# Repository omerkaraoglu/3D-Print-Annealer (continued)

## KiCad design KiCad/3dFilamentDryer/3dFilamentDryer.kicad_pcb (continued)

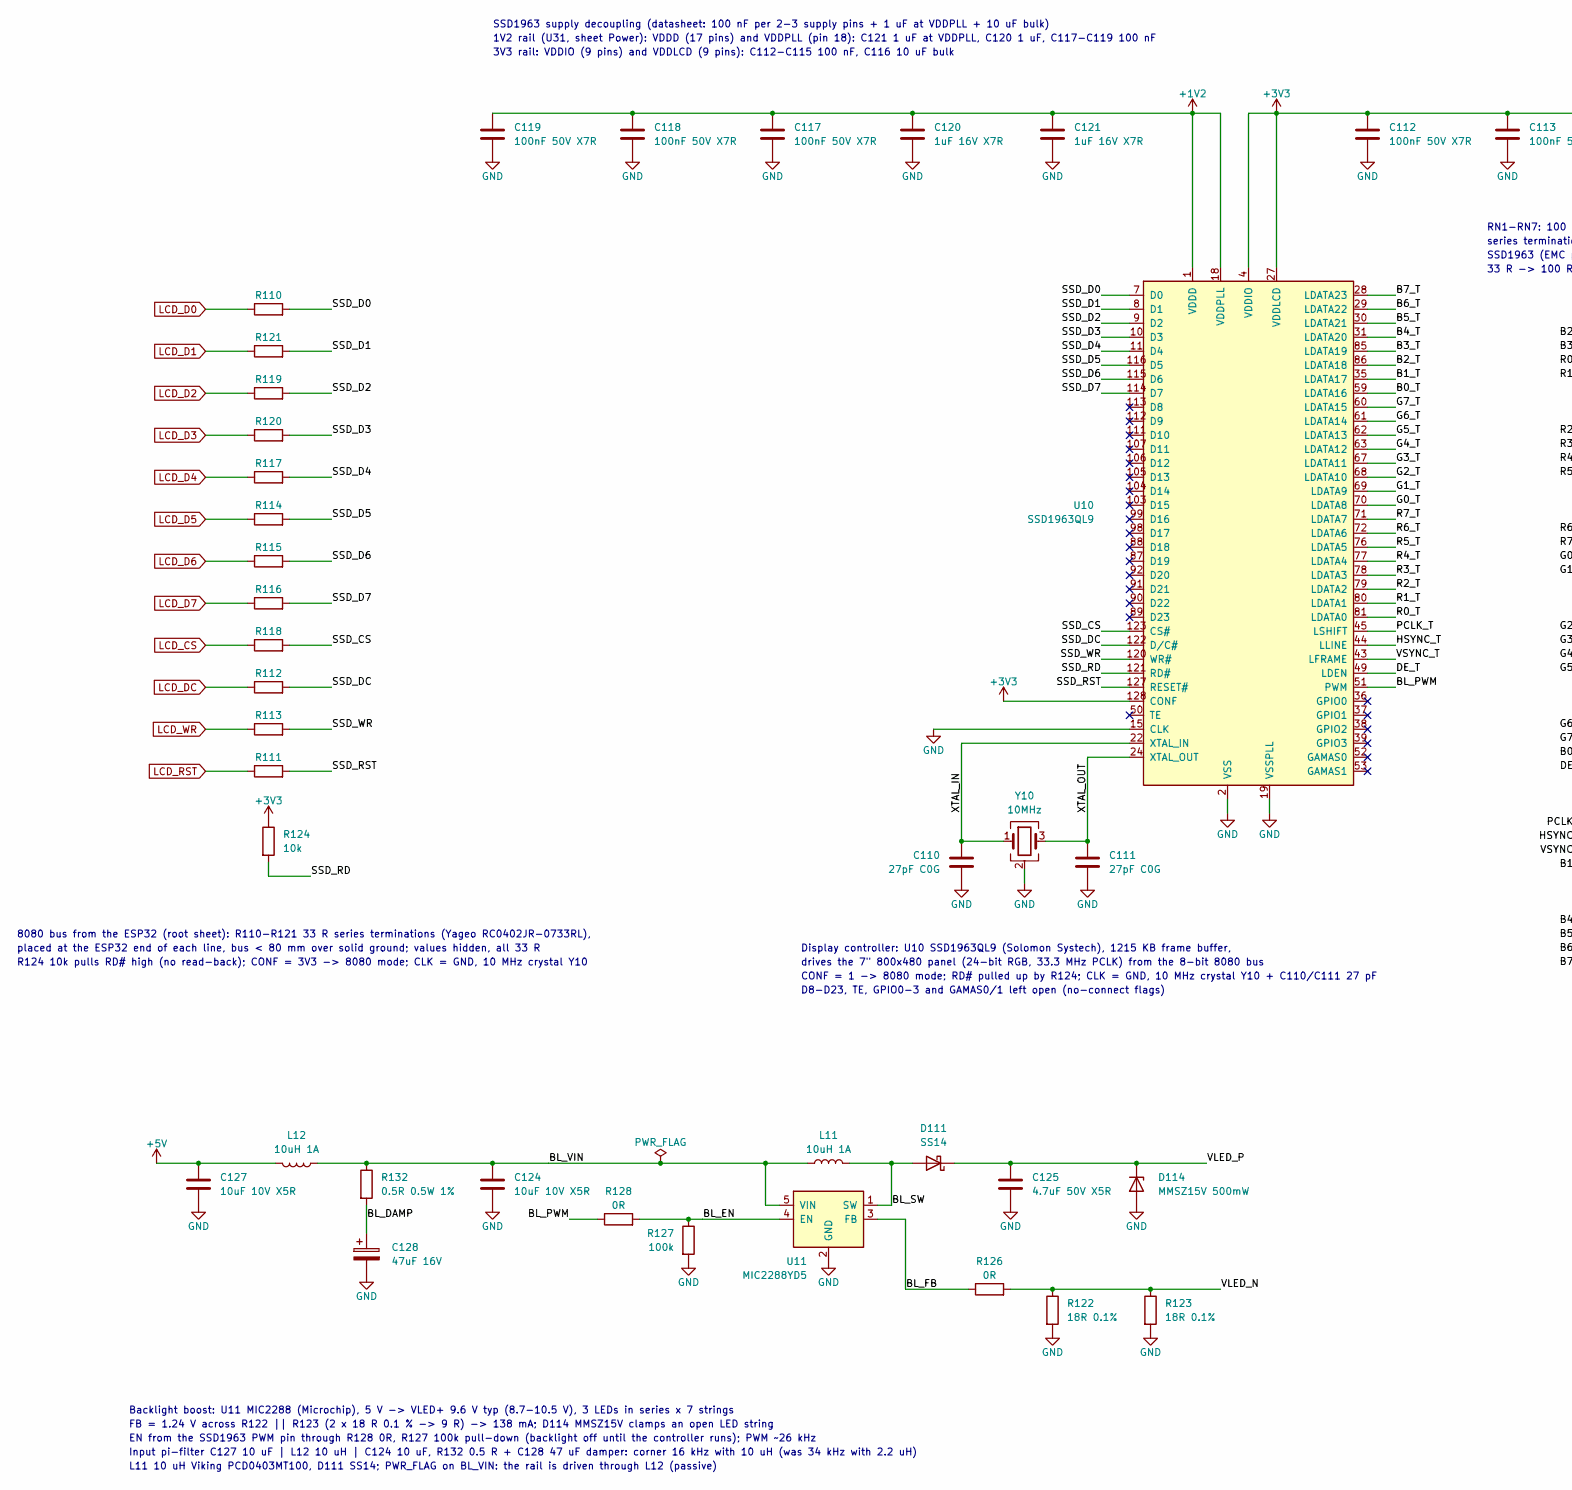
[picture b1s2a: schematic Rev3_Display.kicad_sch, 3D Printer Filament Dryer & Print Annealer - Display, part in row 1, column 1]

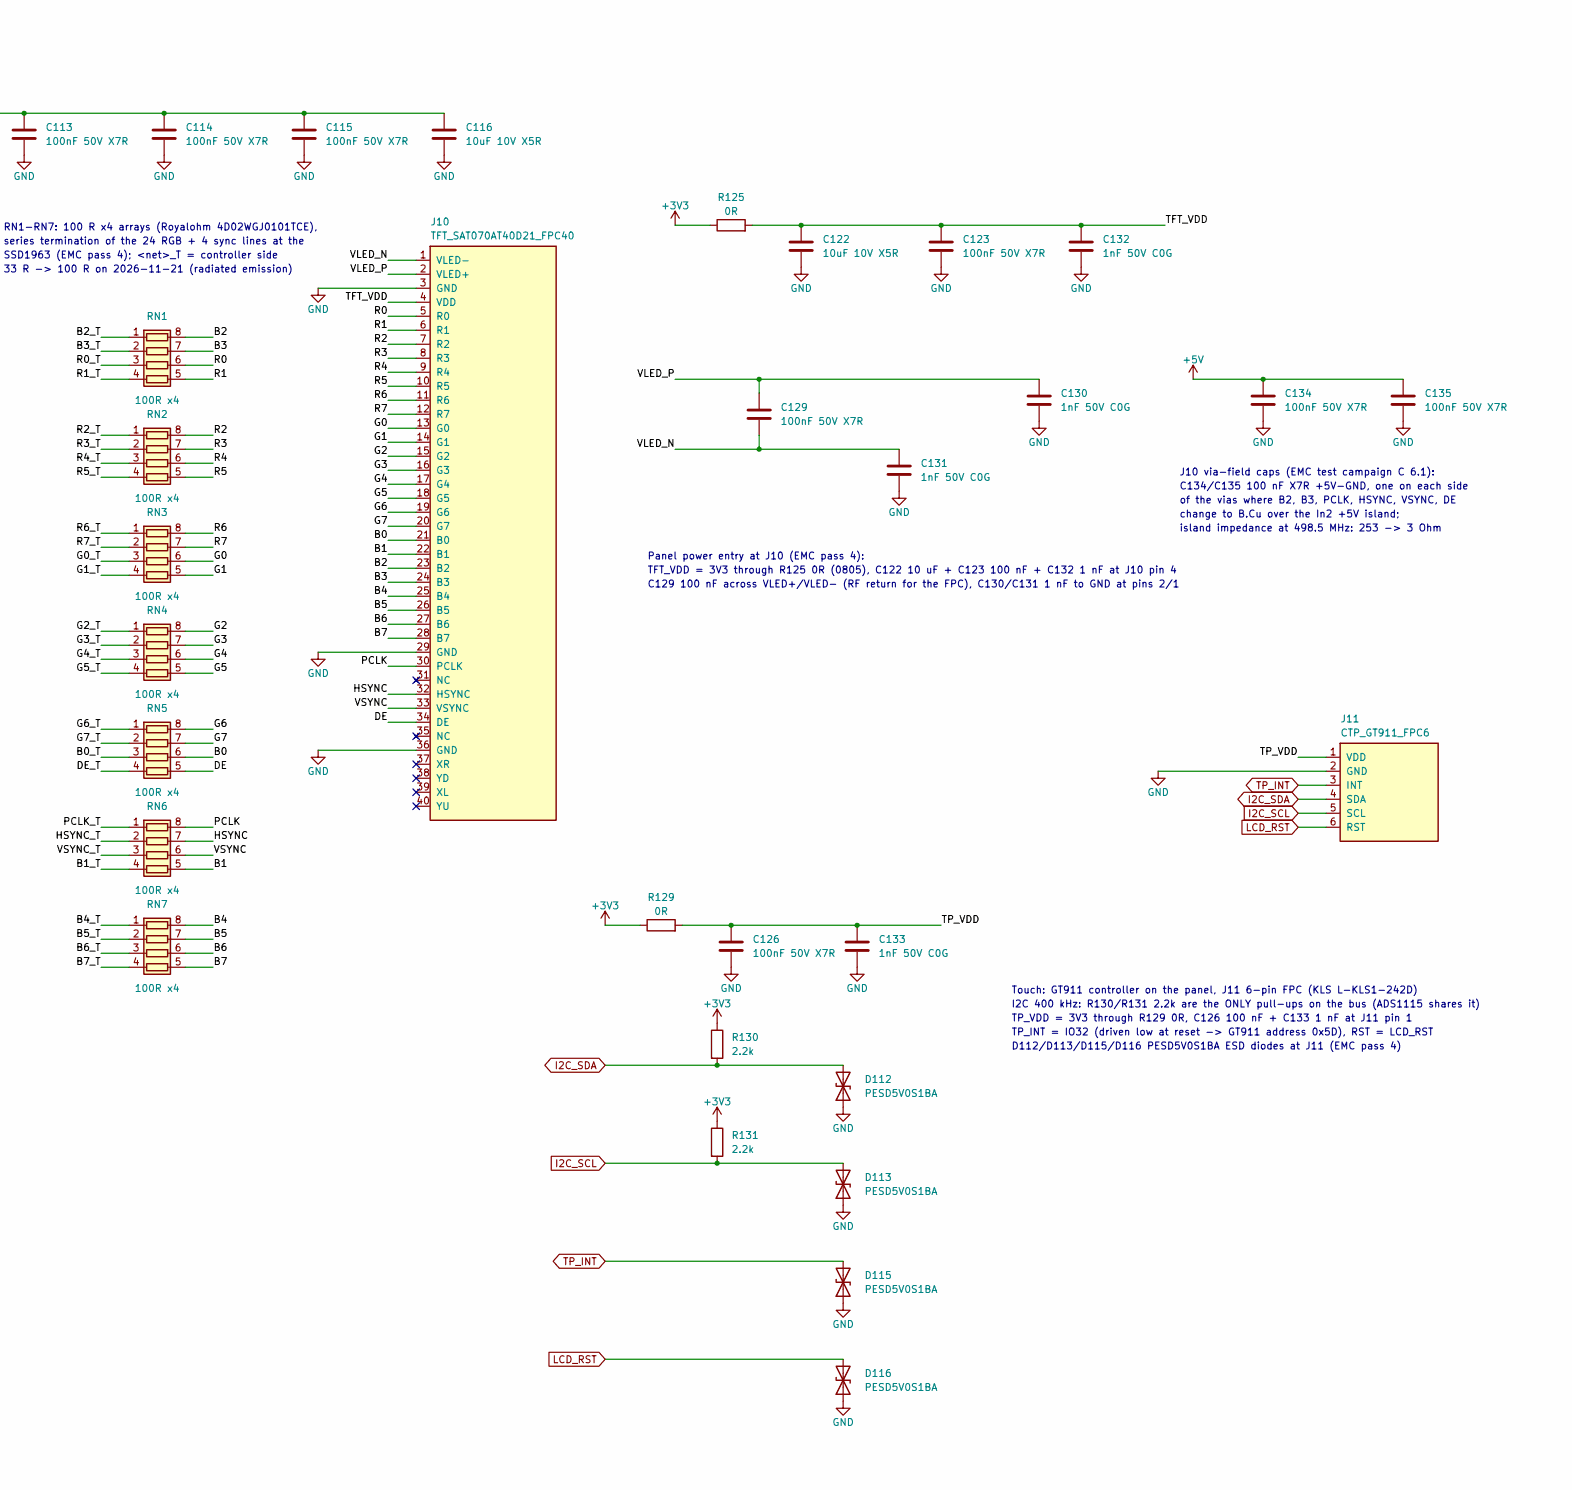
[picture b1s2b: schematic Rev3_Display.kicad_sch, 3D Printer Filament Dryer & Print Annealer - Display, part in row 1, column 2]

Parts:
C110, C111: 27pF C0G; C_0402_1005Metric; MPN GRM1555C1H270JA01D
C112, C113, C114, C115, C117, C118, C119, C123, C126, C129, C134, C135: 100nF 50V X7R; C_0402_1005Metric; MPN CC0402KRX7R9BB104
C116, C122, C124, C127: 10uF 10V X5R; C_0805_2012Metric; MPN CL21A106KPFNNNE
C120, C121: 1uF 16V X7R; C_0603_1608Metric; MPN C1608X7R1C105K080AC
C125: 4.7uF 50V X5R; C_0805_2012Metric; MPN CL21A475KBQNNNE
C128: 47uF 16V; CP_Elec_5x5.4; MPN EEEFK1C470UR
C130, C131, C132, C133: 1nF 50V C0G; C_0402_1005Metric; MPN CL05C102JB5NNNC
D111: SS14; D_SMA; MPN SS14-SMA-N-JQ
D112, D113, D115, D116: PESD5V0S1BA; D_SOD-323; MPN PESD5V0S1BA,115
D114: MMSZ15V 500mW; D_SOD-123; MPN MMSZ15V-HT
J10: TFT_SAT070AT40D21_FPC40; Connfly_DS1020-09-40VBT1B_1x40_P0.5mm_Horizontal_TopSide; MPN DS1020-09-40VBT1B
J11: CTP_GT911_FPC6; KLS_L-KLS1-242D-1.2-06-T-U-R_1x06_P0.5mm_Horizontal_TopSide; MPN L-KLS1-242D-1.2-06-T-U-R
L11, L12: 10uH 1A; L_Viking_PCD0403; MPN PCD0403MT100
R110, R111, R112, R113, R114, R115, R116, R117, R118, R119, R120, R121: 33R; R_0402_1005Metric; MPN RC0402JR-0733RL
R122, R123: 18R 0.1%; R_0805_2012Metric; MPN TC0525B180JT5F
R124: 10k; R_0402_1005Metric; MPN 0402WGJ0103TCE
R125, R129: 0R; R_0805_2012Metric; MPN 0805WAJ0000T5E
R126, R128: 0R; R_0402_1005Metric; MPN CQ02WGJ0000TCE
R127: 100k; R_0402_1005Metric; MPN CQ02WGF1003TCE
R130, R131: 2.2k; R_0402_1005Metric; MPN AC0402JR-072K2L
R132: 0.5R 0.5W 1%; R_1206_3216Metric; MPN HP06W2F500LT5E
RN1, RN2, RN3, RN4, RN5, RN6, RN7: 100R x4; R_Array_Convex_4x0402; MPN 4D02WGJ0101TCE
U10: SSD1963QL9; LQFP-128_14x14mm_P0.4mm; MPN SSD1963QL9
U11: MIC2288YD5; TSOT-23-5; MPN MIC2288YD5-TR
Y10: 10MHz; Crystal_SMD_3225-4Pin_3.2x2.5mm; MPN CX3225GB10000P0HPQCC

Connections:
+1V2: C117.1, C118.1, C119.1, C120.1, C121.1, U10.1 (VDDD), U10.6 (VDDD), U10.14 (VDDD), U10.18 (VDDPLL), U10.21 (VDDD), U10.25 (VDDD), U10.32 (VDDD), U10.40 (VDDD), U10.46 (VDDD), U10.56 (VDDD), U10.64 (VDDD), U10.73 (VDDD), U10.82 (VDDD), U10.93 (VDDD), U10.102 (VDDD), U10.110 (VDDD), U10.119 (VDDD), U10.126 (VDDD); also elsewhere on the board
+3V3: C112.1, C113.1, C114.1, C115.1, C116.1, R124.1, R125.1, R129.1, R130.1, R131.1, U10.4 (VDDIO), U10.12 (VDDIO), U10.16 (VDDIO), U10.27 (VDDLCD), U10.34 (VDDLCD), U10.42 (VDDLCD), U10.48 (VDDLCD), U10.54 (VDDLCD), U10.58 (VDDLCD), U10.66 (VDDLCD), U10.75 (VDDLCD), U10.84 (VDDLCD), U10.95 (VDDIO), U10.97 (VDDIO), U10.100 (VDDIO), U10.108 (VDDIO), U10.117 (VDDIO), U10.124 (VDDIO), U10.128 (CONF); also elsewhere on the board
+5V: C127.1, C134.1, C135.1, L12.2; also elsewhere on the board
/Display/B0: J10.21 (B0), RN5.6 (R3.2)
/Display/B0_T: RN5.3 (R3.1), U10.59 (LDATA16)
/Display/B1: J10.22 (B1), RN6.5 (R4.2)
/Display/B1_T: RN6.4 (R4.1), U10.35 (LDATA17)
/Display/B2: J10.23 (B2), RN1.8 (R1.2)
/Display/B2_T: RN1.1 (R1.1), U10.86 (LDATA18)
/Display/B3: J10.24 (B3), RN1.7 (R2.2)
/Display/B3_T: RN1.2 (R2.1), U10.85 (LDATA19)
/Display/B4: J10.25 (B4), RN7.8 (R1.2)
/Display/B4_T: RN7.1 (R1.1), U10.31 (LDATA20)
/Display/B5: J10.26 (B5), RN7.7 (R2.2)
/Display/B5_T: RN7.2 (R2.1), U10.30 (LDATA21)
/Display/B6: J10.27 (B6), RN7.6 (R3.2)
/Display/B6_T: RN7.3 (R3.1), U10.29 (LDATA22)
/Display/B7: J10.28 (B7), RN7.5 (R4.2)
/Display/B7_T: RN7.4 (R4.1), U10.28 (LDATA23)
/Display/BL_DAMP: C128.1, R132.2
/Display/BL_EN: R127.1, R128.2, U11.4 (EN)
/Display/BL_FB: R126.1, U11.3 (FB)
/Display/BL_PWM: R128.1, U10.51 (PWM)
/Display/BL_SW: D111.2 (A), L11.2, U11.1 (SW)
/Display/BL_VIN: C124.1, L11.1, L12.1, R132.1, U11.5 (VIN)
/Display/DE: J10.34 (DE), RN5.5 (R4.2)
/Display/DE_T: RN5.4 (R4.1), U10.49 (LDEN)
/Display/G0: J10.13 (G0), RN3.6 (R3.2)
/Display/G0_T: RN3.3 (R3.1), U10.70 (LDATA8)
/Display/G1: J10.14 (G1), RN3.5 (R4.2)
/Display/G1_T: RN3.4 (R4.1), U10.69 (LDATA9)
/Display/G2: J10.15 (G2), RN4.8 (R1.2)
/Display/G2_T: RN4.1 (R1.1), U10.68 (LDATA10)
/Display/G3: J10.16 (G3), RN4.7 (R2.2)
/Display/G3_T: RN4.2 (R2.1), U10.67 (LDATA11)
/Display/G4: J10.17 (G4), RN4.6 (R3.2)
/Display/G4_T: RN4.3 (R3.1), U10.63 (LDATA12)
/Display/G5: J10.18 (G5), RN4.5 (R4.2)
/Display/G5_T: RN4.4 (R4.1), U10.62 (LDATA13)
/Display/G6: J10.19 (G6), RN5.8 (R1.2)
/Display/G6_T: RN5.1 (R1.1), U10.61 (LDATA14)
/Display/G7: J10.20 (G7), RN5.7 (R2.2)
/Display/G7_T: RN5.2 (R2.1), U10.60 (LDATA15)
/Display/HSYNC: J10.32 (HSYNC), RN6.7 (R2.2)
/Display/HSYNC_T: RN6.2 (R2.1), U10.44 (LLINE)
/Display/PCLK: J10.30 (PCLK), RN6.8 (R1.2)
/Display/PCLK_T: RN6.1 (R1.1), U10.45 (LSHIFT)
/Display/R0: J10.5 (R0), RN1.6 (R3.2)
/Display/R0_T: RN1.3 (R3.1), U10.81 (LDATA0)
/Display/R1: J10.6 (R1), RN1.5 (R4.2)
/Display/R1_T: RN1.4 (R4.1), U10.80 (LDATA1)
/Display/R2: J10.7 (R2), RN2.8 (R1.2)
/Display/R2_T: RN2.1 (R1.1), U10.79 (LDATA2)
/Display/R3: J10.8 (R3), RN2.7 (R2.2)
/Display/R3_T: RN2.2 (R2.1), U10.78 (LDATA3)
/Display/R4: J10.9 (R4), RN2.6 (R3.2)
/Display/R4_T: RN2.3 (R3.1), U10.77 (LDATA4)
/Display/R5: J10.10 (R5), RN2.5 (R4.2)
/Display/R5_T: RN2.4 (R4.1), U10.76 (LDATA5)
/Display/R6: J10.11 (R6), RN3.8 (R1.2)
/Display/R6_T: RN3.1 (R1.1), U10.72 (LDATA6)
/Display/R7: J10.12 (R7), RN3.7 (R2.2)
/Display/R7_T: RN3.2 (R2.1), U10.71 (LDATA7)
/Display/SSD_CS: R118.2, U10.123 (CS#)
/Display/SSD_D0: R110.2, U10.7 (D0)
/Display/SSD_D1: R121.2, U10.8 (D1)
/Display/SSD_D2: R119.2, U10.9 (D2)
/Display/SSD_D3: R120.2, U10.10 (D3)
/Display/SSD_D4: R117.2, U10.11 (D4)
/Display/SSD_D5: R114.2, U10.116 (D5)
/Display/SSD_D6: R115.2, U10.115 (D6)
/Display/SSD_D7: R116.2, U10.114 (D7)
/Display/SSD_DC: R112.2, U10.122 (D/C#)
/Display/SSD_RD: R124.2, U10.121 (RD#)
/Display/SSD_RST: R111.2, U10.127 (RESET#)
/Display/SSD_WR: R113.2, U10.120 (WR#)
/Display/TFT_VDD: C122.1, C123.1, C132.1, J10.4 (VDD), R125.2
/Display/TP_VDD: C126.1, C133.1, J11.1 (VDD), R129.2
/Display/VLED_N: C129.2, C131.1, J10.1 (VLED-), R122.1, R123.1, R126.2
/Display/VLED_P: C125.1, C129.1, C130.1, D111.1 (K), D114.1 (K), J10.2 (VLED+)
/Display/VSYNC: J10.33 (VSYNC), RN6.6 (R3.2)
/Display/VSYNC_T: RN6.3 (R3.1), U10.43 (LFRAME)
/Display/XTAL_IN: C110.1, U10.22 (XTAL_IN), Y10.1
/Display/XTAL_OUT: C111.1, U10.24 (XTAL_OUT), Y10.3
GND: C110.2, C111.2, C112.2, C113.2, C114.2, C115.2, C116.2, C117.2, C118.2, C119.2, C120.2, C121.2, C122.2, C123.2, C124.2, C125.2, C126.2, C127.2, C128.2, C130.2, C131.2, C132.2, C133.2, C134.2, C135.2, D112.1 (A1), D113.1 (A1), D114.2 (A), D115.1 (A1), D116.1 (A1), J10.3 (GND), J10.29 (GND), J10.36 (GND), J11.2 (GND), R122.2, R123.2, R127.2, U10.2 (VSS), U10.3 (VSS), U10.5 (VSS), U10.13 (VSS), U10.15 (CLK), U10.17 (VSS), U10.19 (VSSPLL), U10.20 (VSS), U10.23 (VSS), U10.26 (VSS), U10.33 (VSS), U10.41 (VSS), U10.47 (VSS), U10.55 (VSS), U10.57 (VSS), U10.65 (VSS), U10.74 (VSS), U10.83 (VSS), U10.94 (VSS), U10.96 (VSS), U10.101 (VSS), U10.109 (VSS), U10.118 (VSS), U10.125 (VSS), U11.2 (GND), Y10.2 (G), Y10.4 (G); also elsewhere on the board
I2C_SCL: D113.2 (A2), J11.5 (SCL), R131.2; also elsewhere on the board
I2C_SDA: D112.2 (A2), J11.4 (SDA), R130.2; also elsewhere on the board
LCD_CS: R118.1; also elsewhere on the board
LCD_D0: R110.1; also elsewhere on the board
LCD_D1: R121.1; also elsewhere on the board
LCD_D2: R119.1; also elsewhere on the board
LCD_D3: R120.1; also elsewhere on the board
LCD_D4: R117.1; also elsewhere on the board
LCD_D5: R114.1; also elsewhere on the board
LCD_D6: R115.1; also elsewhere on the board
LCD_D7: R116.1; also elsewhere on the board
LCD_DC: R112.1; also elsewhere on the board
LCD_RST: D116.2 (A2), J11.6 (RST), R111.1; also elsewhere on the board
LCD_WR: R113.1; also elsewhere on the board
TP_INT: D115.2 (A2), J11.3 (INT); also elsewhere on the board

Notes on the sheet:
Display controller: U10 SSD1963QL9 (Solomon Systech), 1215 KB frame buffer,
drives the 7" 800x480 panel (24-bit RGB, 33.3 MHz PCLK) from the 8-bit 8080 bus
CONF = 1 -> 8080 mode; RD# pulled up by R124; CLK = GND, 10 MHz crystal Y10 + C110/C111 27 pF
D8-D23, TE, GPIO0-3 and GAMAS0/1 left open (no-connect flags)
SSD1963 supply decoupling (datasheet: 100 nF per 2-3 supply pins + 1 uF at VDDPLL + 10 uF bulk)
1V2 rail (U31, sheet Power): VDDD (17 pins) and VDDPLL (pin 18): C121 1 uF at VDDPLL, C120 1 uF, C117-C119 100 nF
3V3 rail: VDDIO (9 pins) and VDDLCD (9 pins): C112-C115 100 nF, C116 10 uF bulk
8080 bus from the ESP32 (root sheet): R110-R121 33 R series terminations (Yageo RC0402JR-0733RL),
placed at the ESP32 end of each line, bus < 80 mm over solid ground; values hidden, all 33 R
R124 10k pulls RD# high (no read-back); CONF = 3V3 -> 8080 mode; CLK = GND, 10 MHz crystal Y10
RN1-RN7: 100 R x4 arrays (Royalohm 4D02WGJ0101TCE),
series termination of the 24 RGB + 4 sync lines at the
SSD1963 (EMC pass 4); <net>_T = controller side
33 R -> 100 R on 2026-11-21 (radiated emission)
Panel power entry at J10 (EMC pass 4):
TFT_VDD = 3V3 through R125 0R (0805), C122 10 uF + C123 100 nF + C132 1 nF at J10 pin 4
C129 100 nF across VLED+/VLED- (RF return for the FPC), C130/C131 1 nF to GND at pins 2/1
J10 via-field caps (EMC test campaign C 6.1):
C134/C135 100 nF X7R +5V-GND, one on each side
of the vias where B2, B3, PCLK, HSYNC, VSYNC, DE
change to B.Cu over the In2 +5V island;
island impedance at 498.5 MHz: 253 -> 3 Ohm
Touch: GT911 controller on the panel, J11 6-pin FPC (KLS L-KLS1-242D)
I2C 400 kHz: R130/R131 2.2k are the ONLY pull-ups on the bus (ADS1115 shares it)
TP_VDD = 3V3 through R129 0R, C126 100 nF + C133 1 nF at J11 pin 1
TP_INT = IO32 (driven low at reset -> GT911 address 0x5D), RST = LCD_RST
D112/D113/D115/D116 PESD5V0S1BA ESD diodes at J11 (EMC pass 4)
Backlight boost: U11 MIC2288 (Microchip), 5 V -> VLED+ 9.6 V typ (8.7-10.5 V), 3 LEDs in series x 7 strings
FB = 1.24 V across R122 || R123 (2 x 18 R 0.1 % -> 9 R) -> 138 mA; D114 MMSZ15V clamps an open LED string
EN from the SSD1963 PWM pin through R128 0R, R127 100k pull-down (backlight off until the controller runs); PWM ~26 kHz
Input pi-filter C127 10 uF | L12 10 uH | C124 10 uF, R132 0.5 R + C128 47 uF damper: corner 16 kHz with 10 uH (was 34 kHz with 2.2 uH)
L11 10 uH Viking PCD0403MT100, D111 SS14; PWR_FLAG on BL_VIN: the rail is driven through L12 (passive)

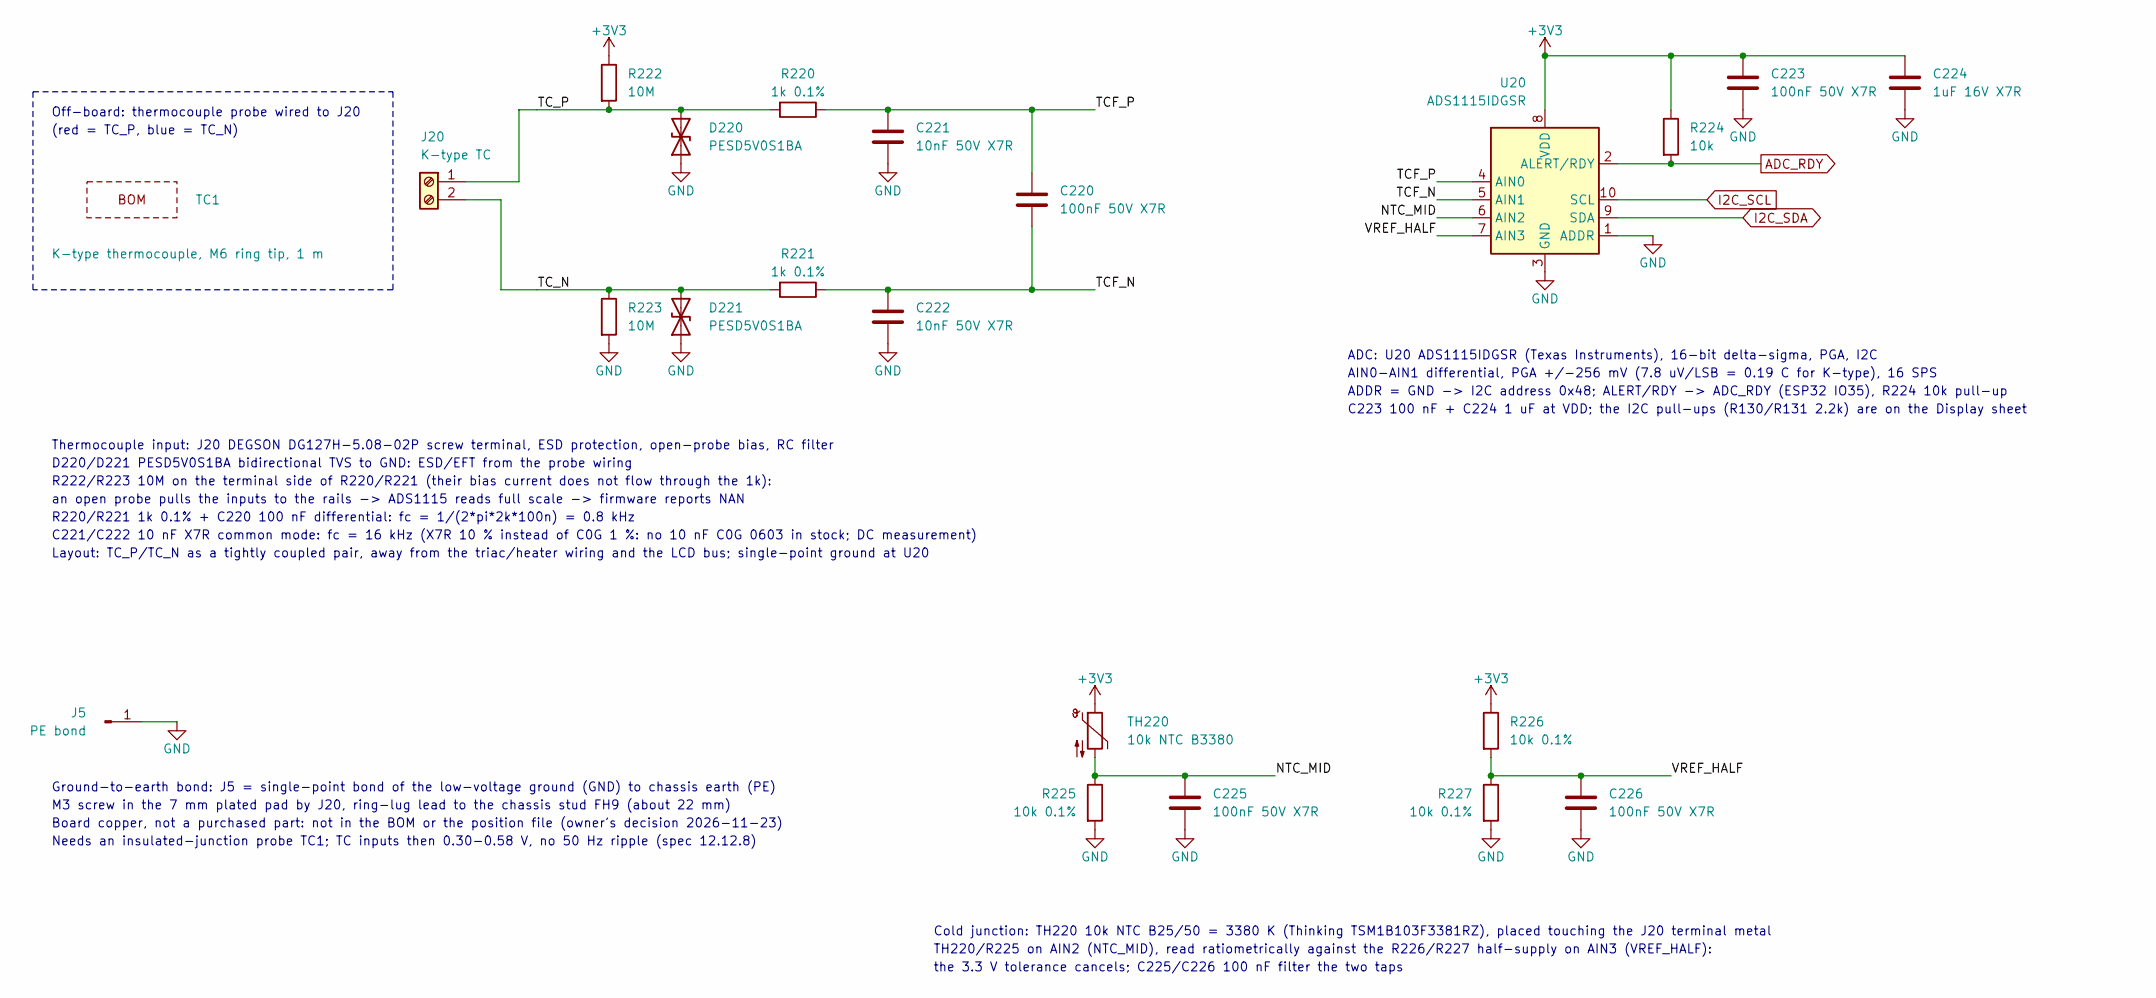
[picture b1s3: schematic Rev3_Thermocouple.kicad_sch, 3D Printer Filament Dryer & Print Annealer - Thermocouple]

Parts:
C220: 100nF 50V X7R; C_0603_1608Metric; MPN CC0603KRX7R9BB104
C221, C222: 10nF 50V X7R; C_0603_1608Metric; MPN CL10B103KB8NNNC
C223, C225, C226: 100nF 50V X7R; C_0402_1005Metric; MPN CC0402KRX7R9BB104
C224: 1uF 16V X7R; C_0603_1608Metric; MPN C1608X7R1C105K080AC
D220, D221: PESD5V0S1BA; D_SOD-323; MPN PESD5V0S1BA,115
J5: PE bond; EarthBond_M3_Pad7.0mm_Drill3.2mm
J20: K-type TC; TerminalBlock_DEGSON_DG127H-5.08-02P; MPN DG127H-5.08-02P-14-00AH
R220, R221: 1k 0.1%; R_0603_1608Metric; MPN TC0325B1001T5F
R222, R223: 10M; R_0603_1608Metric; MPN 0603SAJ0106T5E
R224: 10k; R_0402_1005Metric; MPN 0402WGJ0103TCE
R225, R226, R227: 10k 0.1%; R_0603_1608Metric; MPN TC0325B1002T5F
TC1: K-type thermocouple, M6 ring tip, 1 m; MPN WRNT-02
TH220: 10k NTC B3380; R_0603_1608Metric; MPN TSM1B103F3381RZ
U20: ADS1115IDGSR; TSSOP-10_3x3mm_P0.5mm; MPN ADS1115IDGSR

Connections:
+3V3: C223.1, C224.1, R222.1, R224.1, R226.1, TH220.1, U20.8 (VDD); also elsewhere on the board
/Thermocouple front end (K-type, ADS1115)/NTC_MID: C225.1, R225.1, TH220.2, U20.6 (AIN2)
/Thermocouple front end (K-type, ADS1115)/TCF_N: C220.2, C222.1, R221.1, U20.5 (AIN1)
/Thermocouple front end (K-type, ADS1115)/TCF_P: C220.1, C221.1, R220.1, U20.4 (AIN0)
/Thermocouple front end (K-type, ADS1115)/TC_N: D221.2 (A2), J20.2, R221.2, R223.1
/Thermocouple front end (K-type, ADS1115)/TC_P: D220.2 (A2), J20.1, R220.2, R222.2
/Thermocouple front end (K-type, ADS1115)/VREF_HALF: C226.1, R226.2, R227.1, U20.7 (AIN3)
ADC_RDY: R224.2, U20.2 (ALERT/RDY); also elsewhere on the board
GND: C221.2, C222.2, C223.2, C224.2, C225.2, C226.2, D220.1 (A1), D221.1 (A1), J5.1, R223.2, R225.2, R227.2, U20.1 (ADDR), U20.3 (GND); also elsewhere on the board
I2C_SCL: U20.10 (SCL); also elsewhere on the board
I2C_SDA: U20.9 (SDA); also elsewhere on the board

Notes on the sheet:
Ground-to-earth bond: J5 = single-point bond of the low-voltage ground (GND) to chassis earth (PE)
M3 screw in the 7 mm plated pad by J20, ring-lug lead to the chassis stud FH9 (about 22 mm)
Board copper, not a purchased part: not in the BOM or the position file (owner's decision 2026-11-23)
Needs an insulated-junction probe TC1; TC inputs then 0.30-0.58 V, no 50 Hz ripple (spec 12.12.8)
Off-board: thermocouple probe wired to J20
(red = TC_P, blue = TC_N)
Thermocouple input: J20 DEGSON DG127H-5.08-02P screw terminal, ESD protection, open-probe bias, RC filter
D220/D221 PESD5V0S1BA bidirectional TVS to GND: ESD/EFT from the probe wiring
R222/R223 10M on the terminal side of R220/R221 (their bias current does not flow through the 1k):
an open probe pulls the inputs to the rails -> ADS1115 reads full scale -> firmware reports NAN
R220/R221 1k 0.1% + C220 100 nF differential: fc = 1/(2*pi*2k*100n) = 0.8 kHz
C221/C222 10 nF X7R common mode: fc = 16 kHz (X7R 10 % instead of C0G 1 %: no 10 nF C0G 0603 in stock; DC measurement)
Layout: TC_P/TC_N as a tightly coupled pair, away from the triac/heater wiring and the LCD bus; single-point ground at U20
ADC: U20 ADS1115IDGSR (Texas Instruments), 16-bit delta-sigma, PGA, I2C
AIN0-AIN1 differential, PGA +/-256 mV (7.8 uV/LSB = 0.19 C for K-type), 16 SPS
ADDR = GND -> I2C address 0x48; ALERT/RDY -> ADC_RDY (ESP32 IO35), R224 10k pull-up
C223 100 nF + C224 1 uF at VDD; the I2C pull-ups (R130/R131 2.2k) are on the Display sheet
Cold junction: TH220 10k NTC B25/50 = 3380 K (Thinking TSM1B103F3381RZ), placed touching the J20 terminal metal
TH220/R225 on AIN2 (NTC_MID), read ratiometrically against the R226/R227 half-supply on AIN3 (VREF_HALF):
the 3.3 V tolerance cancels; C225/C226 100 nF filter the two taps

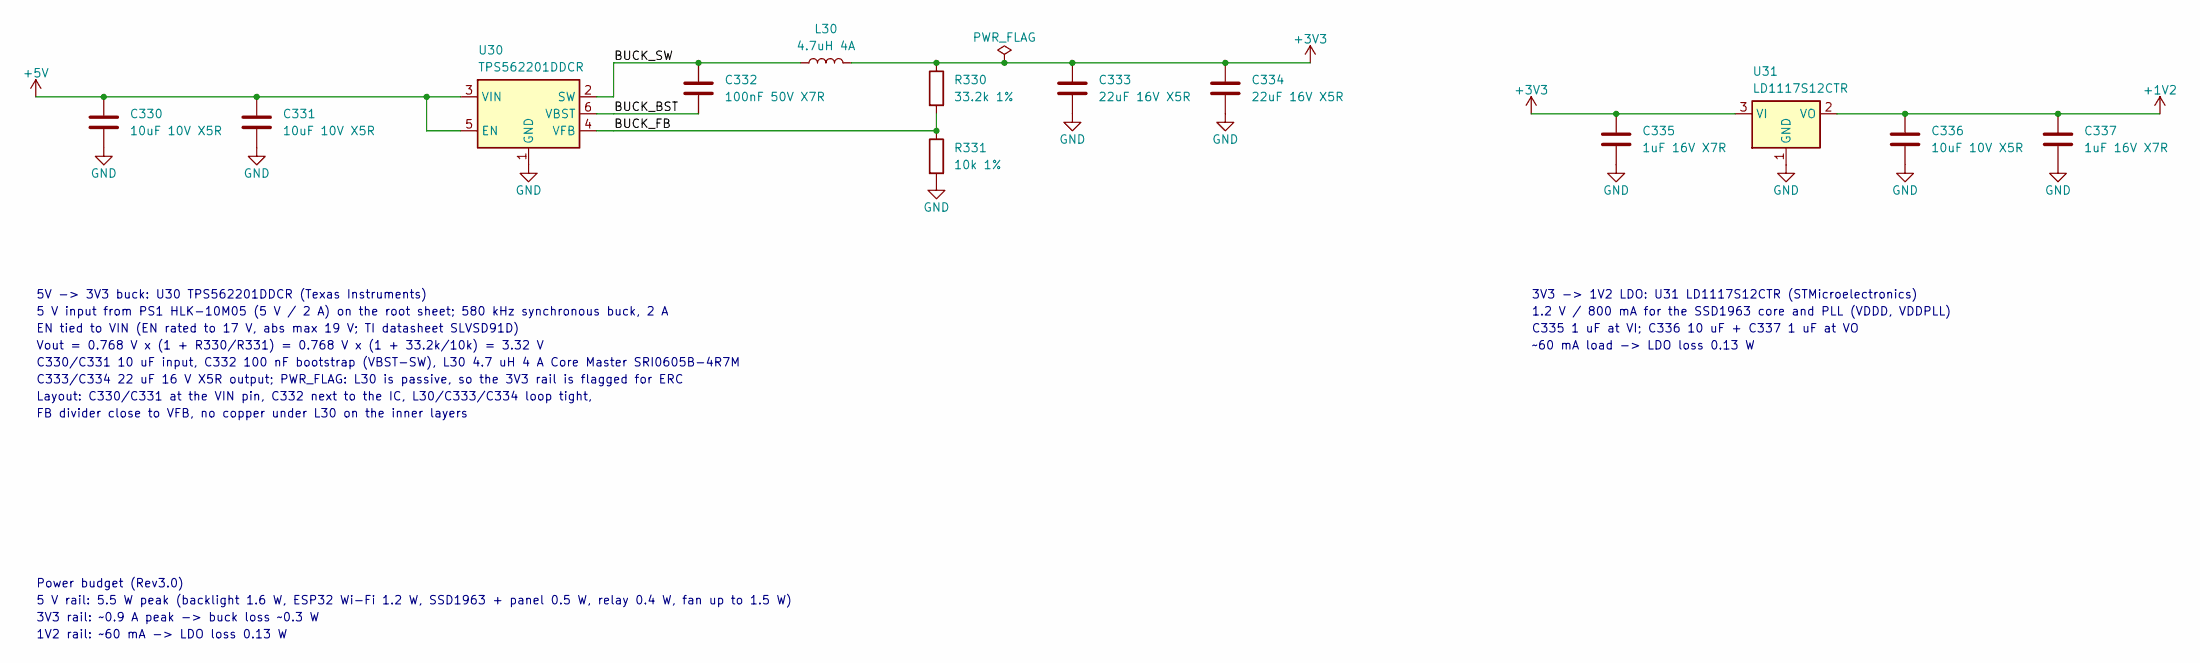
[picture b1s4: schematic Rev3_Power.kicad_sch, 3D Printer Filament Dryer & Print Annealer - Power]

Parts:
C330, C331, C336: 10uF 10V X5R; C_0805_2012Metric; MPN CL21A106KPFNNNE
C332: 100nF 50V X7R; C_0402_1005Metric; MPN CC0402KRX7R9BB104
C333, C334: 22uF 16V X5R; C_0805_2012Metric; MPN CL21A226KOQNNNE
C335, C337: 1uF 16V X7R; C_0603_1608Metric; MPN C1608X7R1C105K080AC
L30: 4.7uH 4A; L_CoreMaster_SRI0605B; MPN SRI0605B-4R7M
R330: 33.2k 1%; R_0402_1005Metric; MPN 0402WGF3322TCE
R331: 10k 1%; R_0402_1005Metric; MPN CQ02WGF1002TCE
U30: TPS562201DDCR; TSOT-23-6; MPN TPS562201DDCR
U31: LD1117S12CTR; SOT-223-3_TabPin2; MPN LD1117S12CTR

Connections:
+1V2: C336.1, C337.1, U31.2 (VO); also elsewhere on the board
+3V3: C333.1, C334.1, C335.1, L30.2, R330.1, U31.3 (VI); also elsewhere on the board
+5V: C330.1, C331.1, U30.3 (VIN), U30.5 (EN); also elsewhere on the board
/Power/BUCK_BST: C332.1, U30.6 (VBST)
/Power/BUCK_FB: R330.2, R331.1, U30.4 (VFB)
/Power/BUCK_SW: C332.2, L30.1, U30.2 (SW)
GND: C330.2, C331.2, C333.2, C334.2, C335.2, C336.2, C337.2, R331.2, U30.1 (GND), U31.1 (GND); also elsewhere on the board

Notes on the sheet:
5V -> 3V3 buck: U30 TPS562201DDCR (Texas Instruments)
5 V input from PS1 HLK-10M05 (5 V / 2 A) on the root sheet; 580 kHz synchronous buck, 2 A
EN tied to VIN (EN rated to 17 V, abs max 19 V; TI datasheet SLVSD91D)
Vout = 0.768 V x (1 + R330/R331) = 0.768 V x (1 + 33.2k/10k) = 3.32 V
C330/C331 10 uF input, C332 100 nF bootstrap (VBST-SW), L30 4.7 uH 4 A Core Master SRI0605B-4R7M
C333/C334 22 uF 16 V X5R output; PWR_FLAG: L30 is passive, so the 3V3 rail is flagged for ERC
Layout: C330/C331 at the VIN pin, C332 next to the IC, L30/C333/C334 loop tight,
FB divider close to VFB, no copper under L30 on the inner layers
3V3 -> 1V2 LDO: U31 LD1117S12CTR (STMicroelectronics)
1.2 V / 800 mA for the SSD1963 core and PLL (VDDD, VDDPLL)
C335 1 uF at VI; C336 10 uF + C337 1 uF at VO
~60 mA load -> LDO loss 0.13 W
Power budget (Rev3.0)
5 V rail: 5.5 W peak (backlight 1.6 W, ESP32 Wi-Fi 1.2 W, SSD1963 + panel 0.5 W, relay 0.4 W, fan up to 1.5 W)
3V3 rail: ~0.9 A peak -> buck loss ~0.3 W
1V2 rail: ~60 mA -> LDO loss 0.13 W

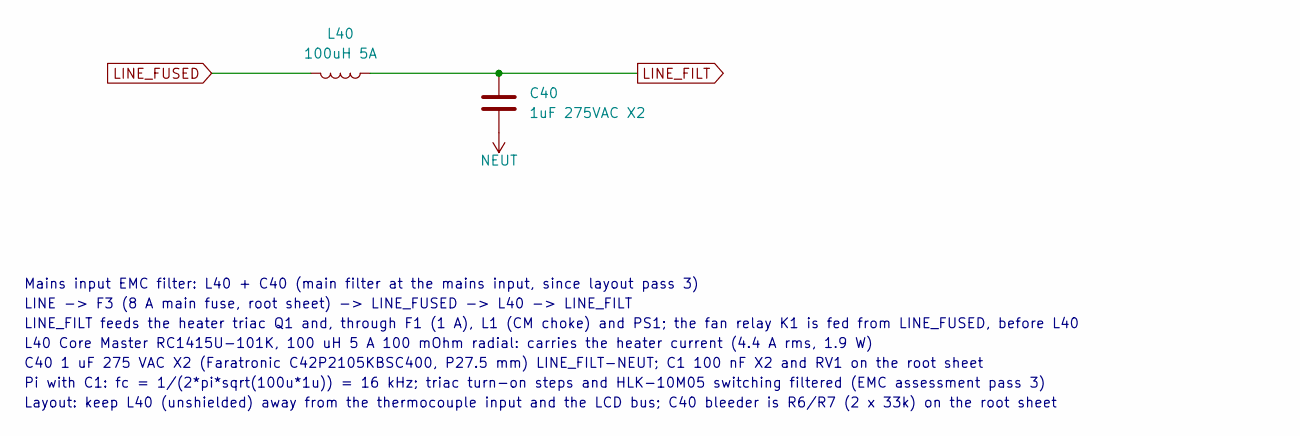
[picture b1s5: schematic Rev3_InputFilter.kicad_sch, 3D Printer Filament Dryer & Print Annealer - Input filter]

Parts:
C40: 1uF 275VAC X2; C_Rect_L32.0mm_W9.0mm_P27.50mm_X2; MPN C42P2105KBSC400
L40: 100uH 5A; L_Radial_CoreMaster_RC1415U; MPN RC1415U-101K

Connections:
LINE_FILT: C40.1, L40.1; also elsewhere on the board
LINE_FUSED: L40.2; also elsewhere on the board
NEUT: C40.2; also elsewhere on the board

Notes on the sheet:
Mains input EMC filter: L40 + C40 (main filter at the mains input, since layout pass 3)
LINE -> F3 (8 A main fuse, root sheet) -> LINE_FUSED -> L40 -> LINE_FILT
LINE_FILT feeds the heater triac Q1 and, through F1 (1 A), L1 (CM choke) and PS1; the fan relay K1 is fed from LINE_FUSED, before L40
L40 Core Master RC1415U-101K, 100 uH 5 A 100 mOhm radial: carries the heater current (4.4 A rms, 1.9 W)
C40 1 uF 275 VAC X2 (Faratronic C42P2105KBSC400, P27.5 mm) LINE_FILT-NEUT; C1 100 nF X2 and RV1 on the root sheet
Pi with C1: fc = 1/(2*pi*sqrt(100u*1u)) = 16 kHz; triac turn-on steps and HLK-10M05 switching filtered (EMC assessment pass 3)
Layout: keep L40 (unshielded) away from the thermocouple input and the LCD bus; C40 bleeder is R6/R7 (2 x 33k) on the root sheet

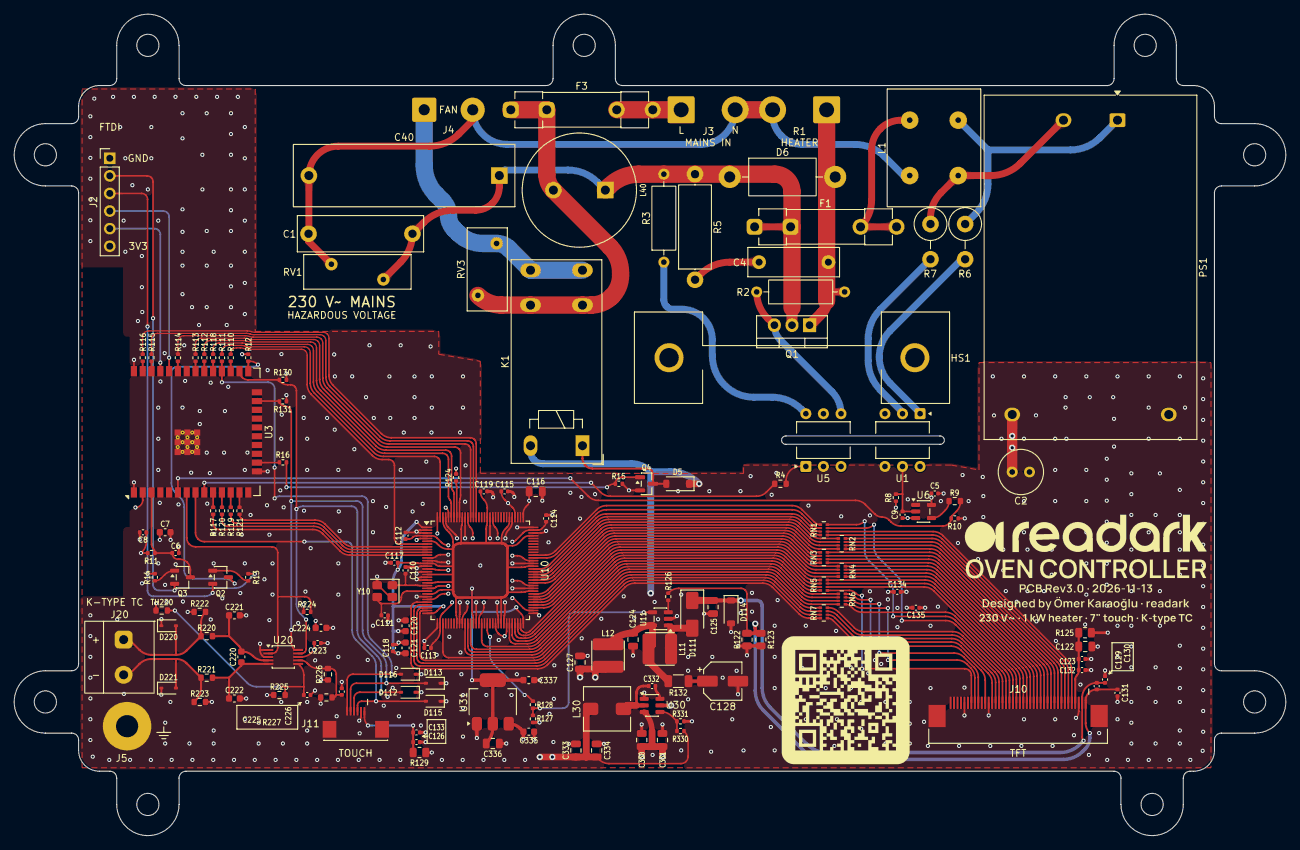
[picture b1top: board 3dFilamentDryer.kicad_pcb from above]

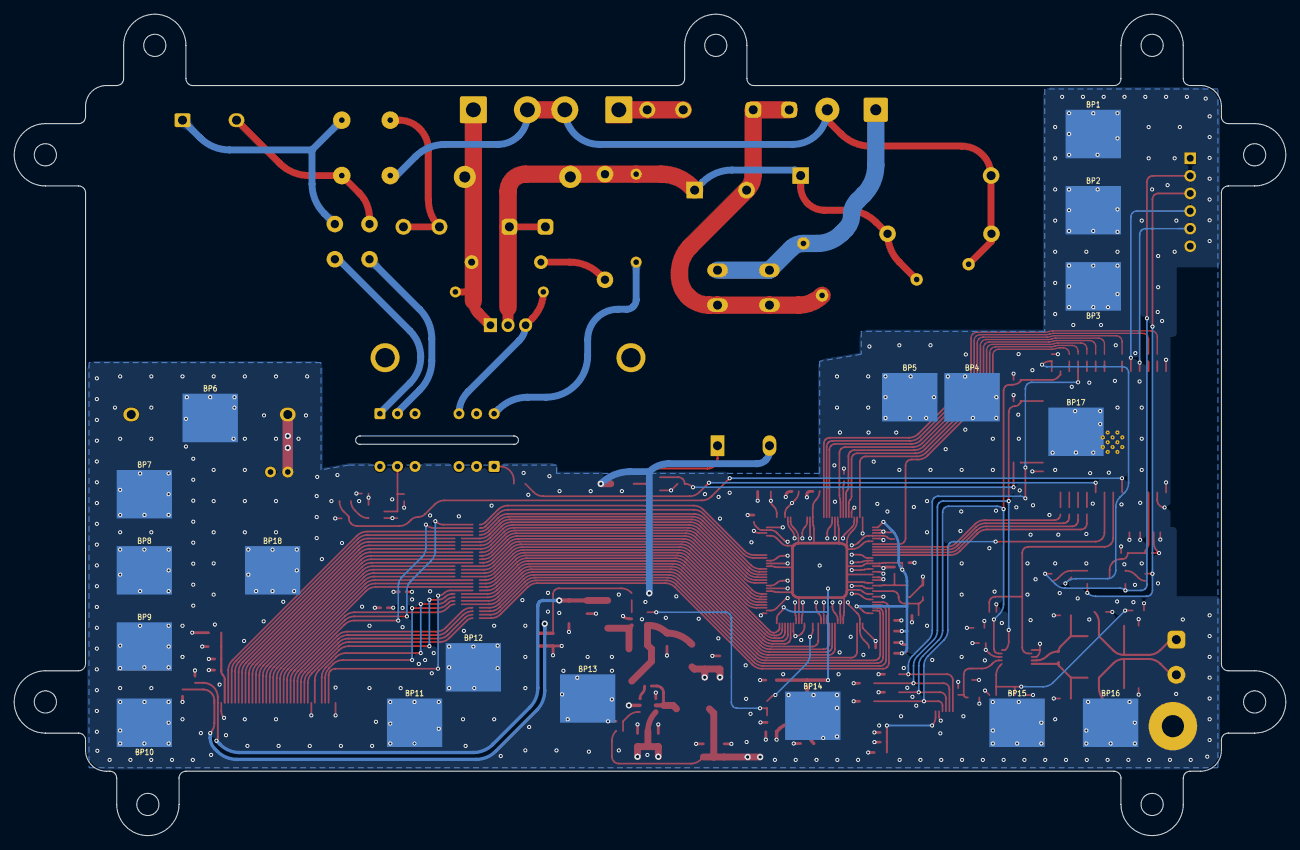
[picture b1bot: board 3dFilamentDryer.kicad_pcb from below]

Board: 4 copper layers, 183.6 x 118.6 mm, 178 parts (19 on the bottom side), 140 nets.

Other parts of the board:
BP1, BP2, BP3, BP4, BP5, BP6, BP7, BP8, BP9, BP10, BP11, BP12, BP13, BP14, BP15, BP16, BP17, BP18: LandingPad_GND; LandingPad_GND_Bare6.0x5.0mm_Cu8.0x7.0mm
DS1: SAT070AT40D21_Mech; TFT7_SAT070AT40D21_Mech
H1, H2, H3, H4, H5, H6, H7, H8, H9: MountingHole_3.2mm_M3

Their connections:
GND: BP1.1, BP2.1, BP3.1, BP4.1, BP5.1, BP6.1, BP7.1, BP8.1, BP9.1, BP10.1, BP11.1, BP12.1, BP13.1, BP14.1, BP15.1, BP16.1, BP17.1, BP18.1; also elsewhere on the board

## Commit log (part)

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2026-03-04 v1.2
2026-03-04 DEsign report updated
2026-04-13 PCB fix
2026-04-27 OTA without CA, factory reset & restore defaults settings added
2026-04-27 OTA with GitHub root CA
2026-04-27 OTA test
2026-04-27 v 2.1.1
2026-04-27 OTA test 2
2026-04-27 v2.1.1
2026-04-30 v2.1.2
2026-06-10 Firmware v2.1.2 Hardware Rev2
